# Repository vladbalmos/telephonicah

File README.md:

# UPDATE
The original version of this project is on branch `original-call-proxy`. The `master` branch doesn't forward calls to a designated number, instead it activates an external connected remote control using the signal port (see the schematic in the `hw` folder for the signal port pinout).
# Telephonicah

This repo contains firmware and hardware related resources (schematic, pcb & enclosure 3d models) for a device used to proxy GSM calls to a designated number (ex: parking barrier gate).

Hardware requirements:

    * Raspberry Pi Pico W
    * SIM800 GSM Module
    * 5V@2.5A power supply
    * capacitors: 100nf, 4.7uf, 2200uf
    * resistors: 2x150ohm, 1Mohm
    * leds: red, green
    
The Pico controls the SIM800 module via UART.

Features:

    * SMS based commands:
        * get remaining credit
        * delete SIM stored SMSs
        * connect to wifi
        * query wifi status
    * Relay received SMS to designated owner number
    * Web UI
    
After the devices connects to WIFI it will bind the webserver to port 8080 and a SMS containing the server's ip address and port will be sent to the administrator's phone number

# System requirements
* micropython
* ampy (pip3 install adafruit-ampy)
* minicom (optional)

# Development

## Linux
Build micropython:

    cd [mycropython-dir]
    make -C mpy-cross

    cd [mycropython-dir]/ports/rp2
    make -j4 BOARD=PICO_W submodules
    make -j4 BOARD=PICO_W clean
    make -j4 BOARD=PICO_W
    
After building copy the micropython firmware to a pico

Init:
    ./setup.sh
    # edit src/phone_numbers.py and add phone numbers
    make build
    
Run:

    make run
    
Clean

    make clean
    
Build

    make build

## Windows
Build micropython https://github.com/micropython/micropython/tree/master/ports/windows

After building copy the micropython firmware to a pico

Edit `build.ps1` and change the $PORT variable to the correct serial port (ex: com1)
Init:

    .\setup.ps1
    # edit src/phone_numbers.py and add phone numbers
    .\build.ps1 -Command build
    
Run:

    .\build.ps1 -Command run

Clean:

    .\build.ps1 -Command clean
    
Build:

    .\build.ps1 -Command build

List files on pico:

    .\build.ps1 -Command list
    
Copy file from pico:

    .\build.ps1 -Command get -Argument [filename]
    
Copy file to pico:

    .\build.ps1 -Command send -Argument [filename]

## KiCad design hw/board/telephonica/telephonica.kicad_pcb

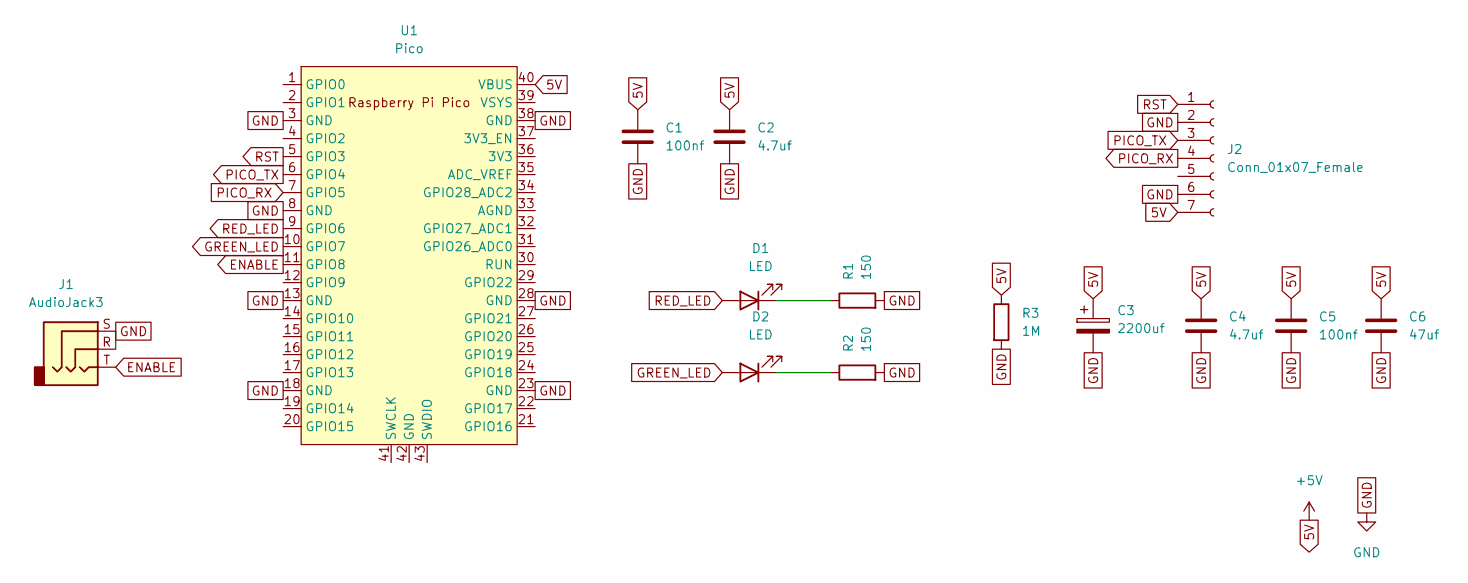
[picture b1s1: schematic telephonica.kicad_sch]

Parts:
C1, C5: 100nf; C_Disc_D3.8mm_W2.6mm_P2.50mm
C2, C4: 4.7uf; C_Disc_D3.8mm_W2.6mm_P2.50mm
C3: 2200uf; C_Radial_D12.5mm_H20.0mm_P5.00mm
C6: 47uf; C_Disc_D3.8mm_W2.6mm_P2.50mm
D1, D2: LED; LED_D5.0mm
J1: AudioJack3; Jack_3.5mm_CUI_SJ1-3525N_Horizontal
J2: Conn_01x07_Female; PinHeader_1x07_P2.54mm_Vertical
R1, R2: 150; R_Axial_DIN0207_L6.3mm_D2.5mm_P7.62mm_Horizontal
R3: 1M; R_Axial_DIN0207_L6.3mm_D2.5mm_P7.62mm_Horizontal
U1: Pico; RPi_Pico_SMD_TH

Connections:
5V: C1.1, C2.1, C3.1, C4.1, C5.1, C6.1, J2.7, R3.1, U1.40 (VBUS)
ENABLE: J1.T, U1.11 (GPIO8)
GND: C1.2, C2.2, C3.2, C4.2, C5.2, C6.2, J1.R, J1.S, J2.2, J2.6, R1.2, R2.2, R3.2, U1.3 (GND), U1.8 (GND), U1.13 (GND), U1.18 (GND), U1.23 (GND), U1.28 (GND), U1.38 (GND)
GREEN_LED: D2.2 (A), U1.10 (GPIO7)
unnamed: D1.1 (K), R1.1
unnamed: D2.1 (K), R2.1
PICO_RX: J2.4, U1.7 (GPIO5)
PICO_TX: J2.3, U1.6 (GPIO4)
RED_LED: D1.2 (A), U1.9 (GPIO6)
RST: J2.1, U1.5 (GPIO3)

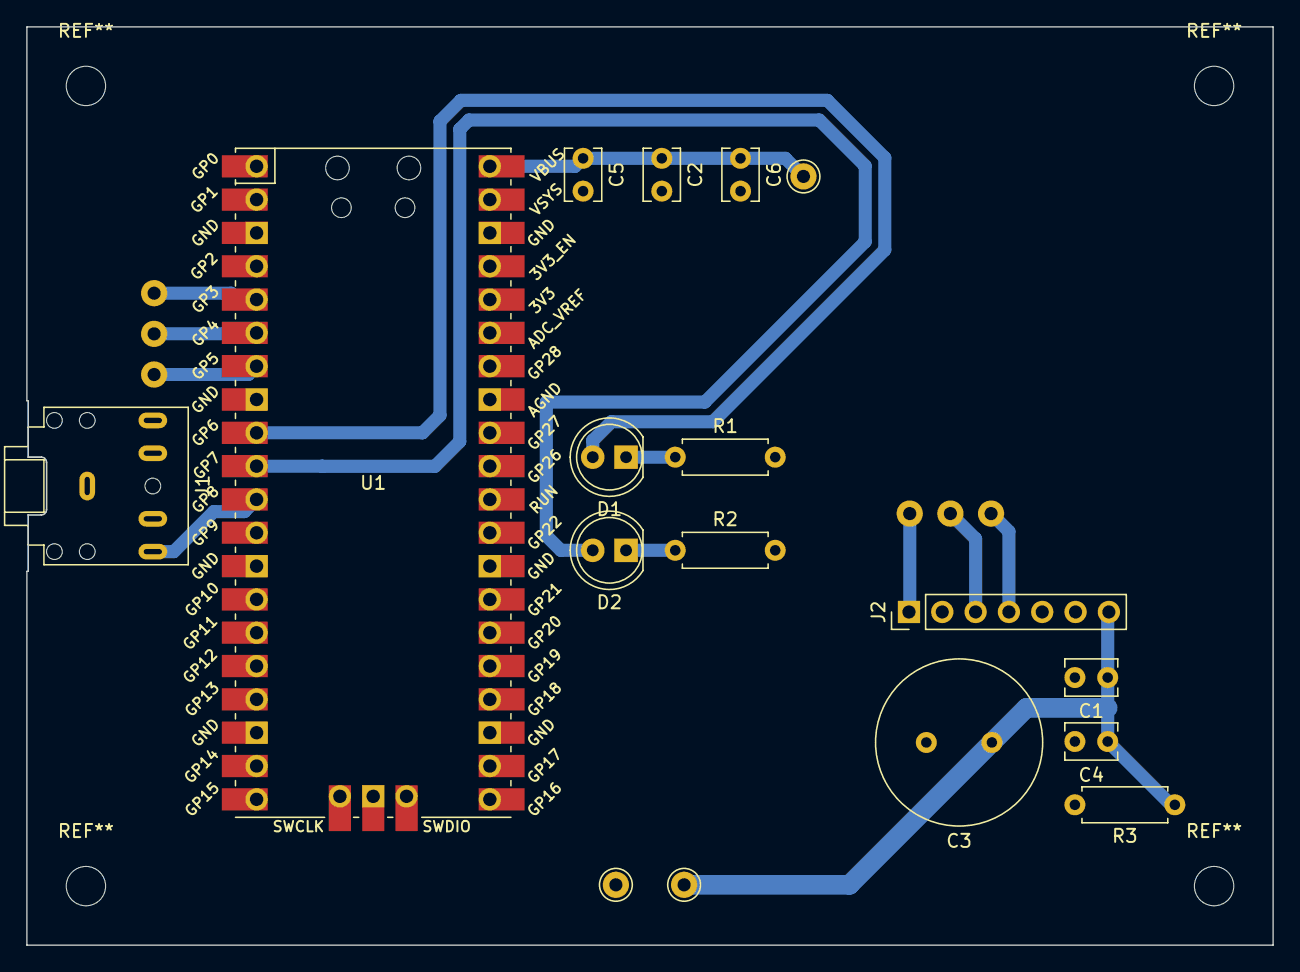
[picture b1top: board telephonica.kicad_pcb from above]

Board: 2 copper layers, 95.0 x 70.0 mm, 14 parts (0 on the bottom side), 10 nets.

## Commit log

2023-04-25 Version 0.9.0 complete
2023-04-27 Add case 3d model
2023-04-28 Update 3d model
2023-04-30 Add hardware resources
2023-05-01 Bug fix
2023-05-01 Update README & final result
2023-05-31 Bug fixes
2023-07-22 Reliability improvements
    * add watchdog to reset device in case of failure
    * increase waiting timeout when calling gate & retry in case of failure
    * store fail logs during call gate procedure
    * retrieve fail logs using webserver
2023-07-22 Update index html template
2023-10-22 Change eof to LF
2024-05-24 Make the duration for setting the enable pin high user configurable
2024-05-29 Bug fixes and improvements
2024-09-16 Add watchdog support
2024-09-16 Remove reset sim functionality
